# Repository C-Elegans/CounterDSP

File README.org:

* uFluidics Counter Project
This repository is the code for the EE4400 uFluidics Counting Project,
for the dsPIC33fj128gp802. To build, make sure MPLAB X and XC16 are
installed, then run 'make'.

** Circuit
   - Chip: dsPIC33fj128gp802 - dip variant
   - ADC connection
     - Pin AN9, package pin 28
   - SPI:
     - SCK: RP12, pin 23
     - MOSI: RP11, pin 22
     - MISO: RP13, pin 24
     - SS_N: RP14, pin 25
   - Passives:
     - 100nF caps: pin 28, pin 20, pin 13
     - 10uF cap: pin 20
       - *This component is REQUIRED to program the chip*
     - 1k pullup on MCLR_N (pin 1)
   - Supply Voltage
     - 3.25V

** Specifications
   - Analog input signal 200mv pk, unknown waveform
   - Amplified to some level 700mv pk?
   - Sampled at 10kHz
   - Cells counted somehow

# ** DONE List [100%]
#    CLOSED: [2018-03-24 Sat 14:36]
#    - [X] Test the features of the chip [100%]
#      - [X] ADC
#      - [X] UART
#      - [X] SPI
#      - [X] DMA [2/2]
#        - [X] UART
#        - [X] ADC
#      - [X] 80MHz Clock
#      - [X] 10kHz timer
#    - [X] Create A mini oscilloscope
#    - [X] Collect simulated waveform
#      - Waveforms are in data/
#    - [X] Analyze simulated data in matlab, determine best counting method
#      - [X] FFT amplitude
#      - [X] Correlation + threshold
#        - [X] Correlation
#        - [X] Create better correlation waveform. Currently just a sine wave, but
# 	     needs to approximate the triangle-y shape of the actual signal
#        - [X] Proper threshold amount
#    - [X] Program above solution on dsp
#      - Collect 256 samples from ADC
#      - Append them to previous 256 samples
#      - Convert samples to complex, pad with 0s to go to 1024 samples
#      - Run FFT
#      - multiply with FFT of the target waveform (stored in program memory)
#      - run IFFT
#      - Threshold + count
     
** Version 0.2 TODO [16%]
   - [ ] Comment code
   - [X] Clean up code
   - [ ] Add display [0%]
     - [ ] Choose display
     - [ ] Find/Write library
     - [ ] Write display routine
   - [ ] Increase number of channels
     - Goal of 3
   - [ ] Reduce memory usage per channel [0%]
     - [ ] Eliminate ping pong buffer
     - [ ] Copy unused data to X memory
     - [ ] Reduce sample storage [0/3]
       - [ ] Do unbatched correlation + threshold
       - [ ] Reduce size of buffers
       - [ ] Reduce sample rate
   - [ ] Design PCB

** Collected data
#+attr_html: :width 500px
[[./data/data2.png]]

A large nail dropped through a straw, sampled at 5kHz
#+attr_html: :width 500px
[[./data/data4.png]]

A small piece of nail dropped through a straw, 5kHz

* Characterization
** With Two cubic magnets
   - 58mV output from coil
   - 30 turns around straw
   - Straw
     - 5.3mm diameter
     - 
   - ??T field strength
     - Can calculate
     - Measure with hall effect sensor

* Amplifier
** Specifications
   - needs gain of 400mV/600nV=660,000
   - Uses AD8428 as low noise input amplifier (g=2000)
   - Uses ADa4528 as final amplifier
     - Feedback resistors set for g=330, Rf=33k, Rg=100\Omega
   - +- 5V power supply
     - May need to do some scaling with a third amp to feed to DSP
** Simulation
   - Outputs 300mV pk/pk for 300nVpk/pk input
   - 1/f Noise at 50mV
#+attr_html: :width 500px
[[./photos/schematic.png]]
#+attr_html: :width 500px
[[./photos/amp1.png]]

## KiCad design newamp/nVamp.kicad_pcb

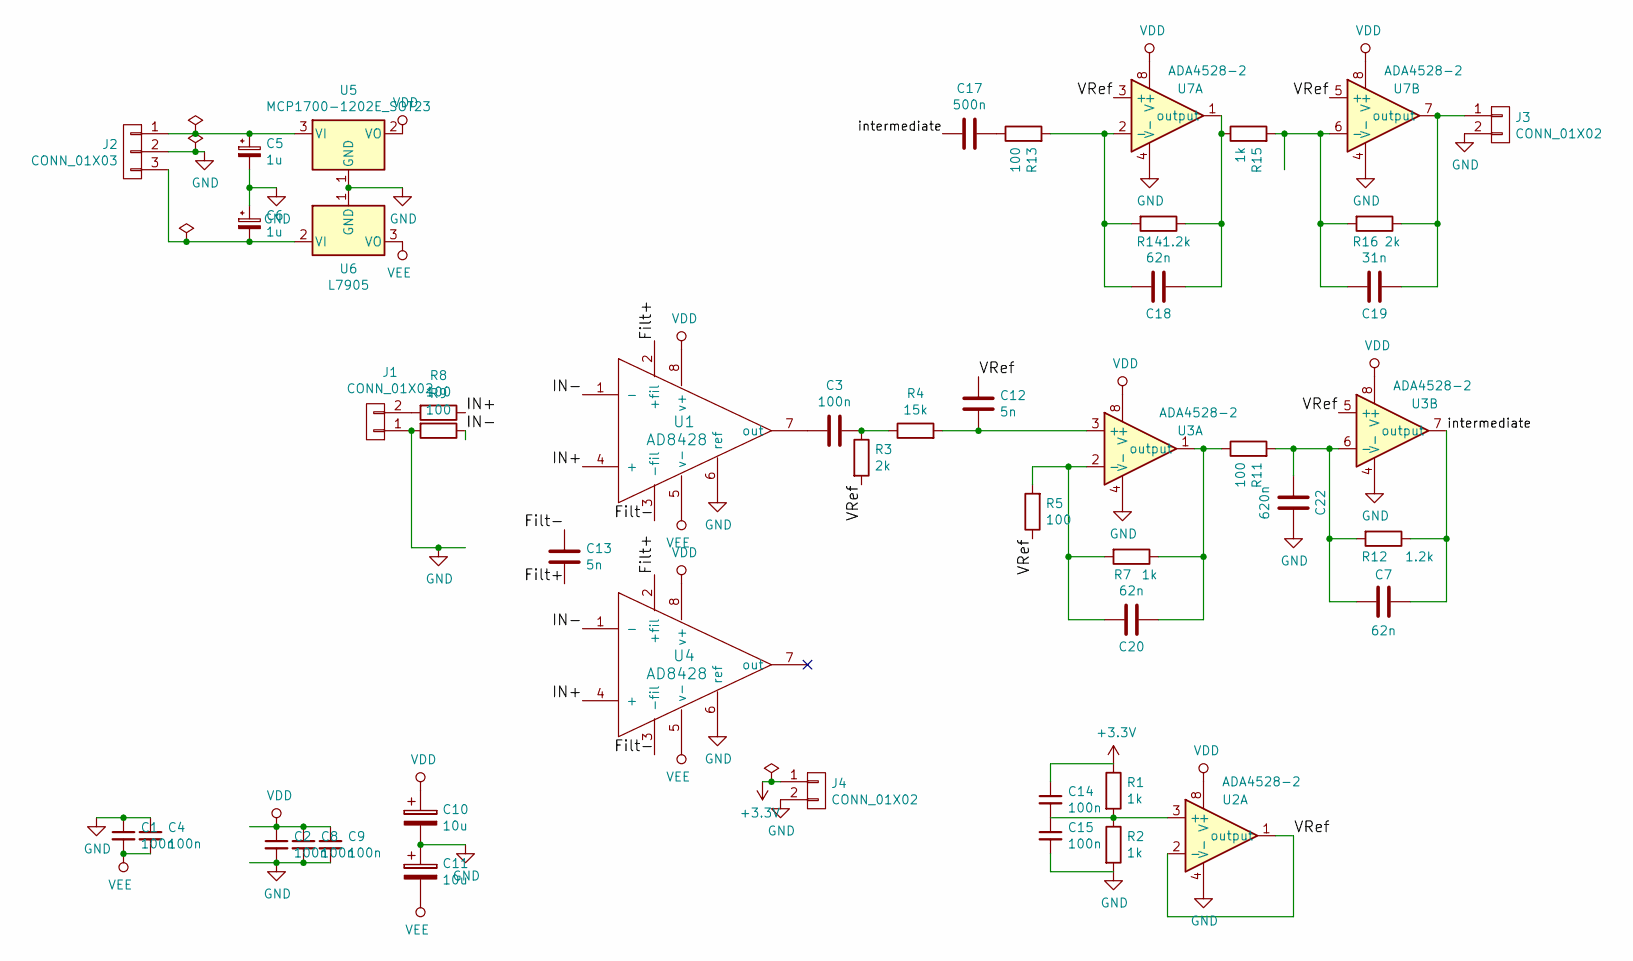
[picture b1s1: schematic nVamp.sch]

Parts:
C1, C2, C3, C4, C8, C9, C14, C15: 100n; C_0603_HandSoldering
C5, C6: 1u; CP_Radial_D5.0mm_P2.50mm
C7, C18, C20: 62n; C_0603_HandSoldering
C10, C11: 10u; CP_Radial_D5.0mm_P2.50mm
C12, C13: 5n; C_0603_HandSoldering
C17: 500n; C_0603_HandSoldering
C19: 31n; C_0603_HandSoldering
C22: 620n; C_0603_HandSoldering
J1, J3, J4: CONN_01X02; Pin_Header_Straight_1x02_Pitch2.54mm
J2: CONN_01X03; Pin_Header_Straight_1x03_Pitch2.54mm
R1, R2, R7, R15: 1k; R_0603_HandSoldering
R3, R16: 2k; R_0603_HandSoldering
R4: 15k; R_0603_HandSoldering
R5, R8, R9, R11, R13: 100; R_0603_HandSoldering
R12, R14: 1.2k; R_0603_HandSoldering
U1, U4: AD8428; SOIC-8_3.9x4.9mm_Pitch1.27mm
U2, U3, U7: ADA4528-2; MSOP-8_3x3mm_Pitch0.65mm
U5: MCP1700-1202E_SOT23; SOT-23
U6: L7905; SOT-89-3

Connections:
+3V3: C14.1, J4.1, R1.1
/Filt+: C13.2, U1.2 (+fil), U4.2 (+fil)
/Filt-: C13.1, U1.3 (-fil), U4.3 (-fil)
/IN+: R8.1, U1.4 (+), U4.4 (+)
/IN-: R9.1, U1.1 (-), U4.1 (-)
/VRef: C12.1, R3.2, R5.1, U2.1 (output), U2.2 (-), U3.5 (+), U7.3 (+), U7.5 (+)
/intermediate: C7.1, C17.2, R12.1, U3.7 (output)
GND: C1.1, C2.2, C4.1, C5.2, C6.1, C8.2, C9.2, C10.2, C11.1, C15.2, C22.1, J1.1, J2.2, J3.2, J4.2, R2.2, R9.2, U1.6 (ref), U2.4 (V-), U3.4 (V-), U4.6 (ref), U5.1 (GND), U6.1 (GND), U7.4 (V-)
unnamed: C3.1, R3.1, R4.1
unnamed: C3.2, U1.7 (out)
unnamed: C5.1, J2.1, U5.3 (VI)
unnamed: C6.2, J2.3, U6.2 (VI)
unnamed: C12.2, R4.2, U3.3 (+)
unnamed: C14.2, C15.1, R1.2, R2.1, U2.3 (+)
unnamed: C17.1, R13.1
unnamed: C18.1, R14.1, R15.1, U7.1 (output)
unnamed: C18.2, R13.2, R14.2, U7.2 (-)
unnamed: C19.1, J3.1, R16.1, U7.7 (output)
unnamed: C19.2, R15.2, R16.2, U7.6 (-)
unnamed: C20.1, R7.1, R11.1, U3.1 (output)
unnamed: C20.2, R5.2, R7.2, U3.2 (-)
unnamed: C7.2, C22.2, R11.2, R12.2, U3.6 (-)
unnamed: J1.2, R8.2
VDD: C2.1, C8.1, C9.1, C10.1, U1.8 (v+), U2.8 (V+), U3.8 (V+), U4.8 (v+), U5.2 (VO), U7.8 (V+)
VEE: C1.2, C4.2, C11.2, U1.5 (v-), U4.5 (v-), U6.3 (VO)

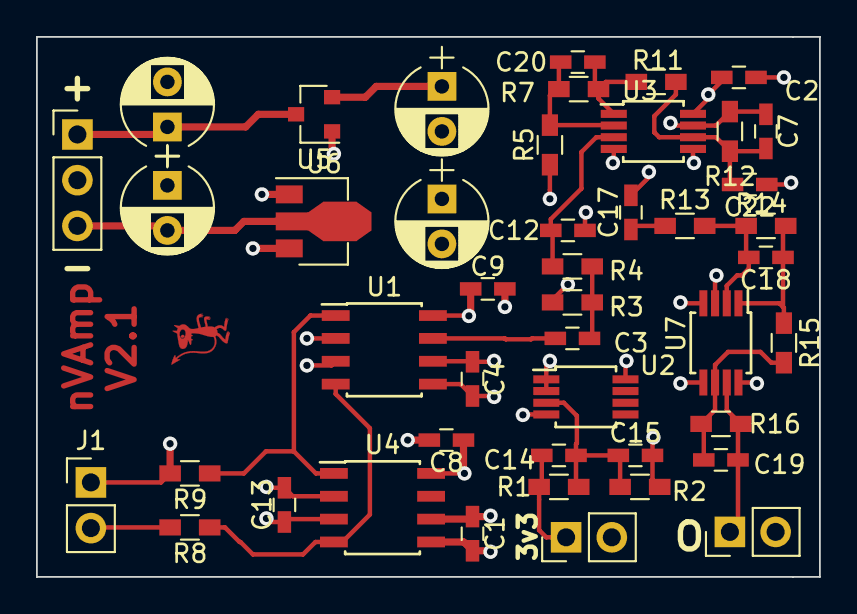
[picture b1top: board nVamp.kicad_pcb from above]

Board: 4 copper layers, 43.5 x 30.0 mm, 45 parts (0 on the bottom side), 25 nets.

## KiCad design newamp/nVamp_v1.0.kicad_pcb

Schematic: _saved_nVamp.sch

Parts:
C1, C2, C4, C5, C6, C7, C8, C9: 100n; C_0603_HandSoldering
C3: 100u; C_1210_HandSoldering
C10, C11: CP; CP_Radial_D8.0mm_P3.50mm
J1, J3, J4: CONN_01X02; Pin_Header_Straight_1x02_Pitch2.54mm
J2: CONN_01X03; Pin_Header_Straight_1x03_Pitch2.54mm
R1, R2: 1k; R_0603_HandSoldering
R3: 15k; R_0603_HandSoldering
R4, R5: 100; R_0603_HandSoldering
R6, R7: 33k; R_0603_HandSoldering
U1, U4: AD8428; SOIC-8_3.9x4.9mm_Pitch1.27mm
U2, U3: ADA4528; TSSOP-8_3x3mm_Pitch0.65mm

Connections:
+3V3: J4.1, R1.1
/Filt+: U1.2 (+fil), U4.2 (+fil)
/Filt-: U1.3 (-fil), U4.3 (-fil)
/IN+: J1.2, U1.4 (+), U4.4 (+)
/VRef: R6.2, U2.2 (-), U2.6
GND: C1.1, C2.2, C4.1, C5.1, C6.1, C7.2, C8.2, C9.2, C10.2, C11.1, J1.1, J2.2, J3.2, J4.2, R2.2, R3.2, R5.1, U1.1 (-), U1.6 (ref), U4.1 (-), U4.6 (ref)
unnamed: C3.1, R3.1, R4.1
unnamed: C3.2, U1.7 (out)
unnamed: J3.1, R7.1, U3.6
unnamed: R1.2, R2.1, U2.3 (+)
unnamed: R4.2, R6.1, U3.3 (+)
unnamed: R5.2, R7.2, U3.2 (-)
VDD: C2.1, C7.1, C8.1, C9.1, C10.1, J2.1, U1.8 (v+), U2.7 (V+), U3.7 (V+), U4.8 (v+)
VEE: C1.2, C4.2, C5.2, C6.2, C11.2, J2.3, U1.5 (v-), U2.4 (V-), U3.4 (V-), U4.5 (v-)

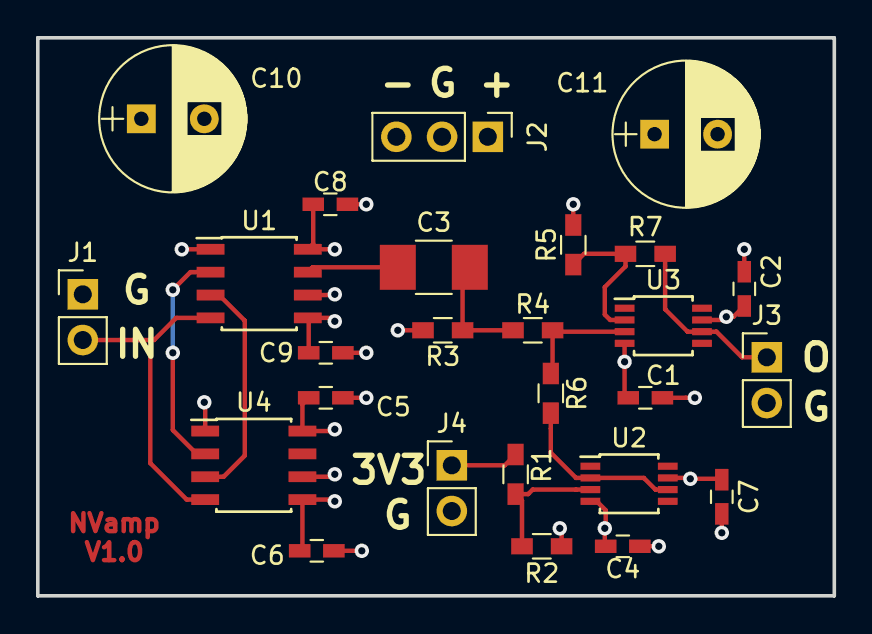
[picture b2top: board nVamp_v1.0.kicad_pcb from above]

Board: 4 copper layers, 44.2 x 31.0 mm, 26 parts (0 on the bottom side), 14 nets.

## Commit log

2017-12-28 Use the MPLib UART functions for printing
2018-01-11 setup ADC to work with DMA
2018-01-11 Move configuration to config.h
2018-01-11 Set DMA to ping pong mode, fix indentation for emacs
2018-01-11 Add some documentation
2018-01-11 Add license and readme
2018-01-12 Get Chip working + UART
2018-01-12 Test adc
2018-01-12 Add TODO list to readme
2018-01-13 Add project configuration to the repo (oops)
2018-01-13 Move peripheral configuration to separate file
2018-01-13 Get SPI working (though very simply)
2018-01-13 Create PLL parameter calculator
2018-01-13 80MHz clock working
    Had some difficulties with programming, turns out a 10uF cap to Vcap
    is required for correct operation.
2018-01-13 Get uart working at 1Mbaud
2018-01-13 ADC DMA transfers working
2018-01-14 Configure ADC to sample off Timer3
    Now ADC samples at 10kHz and the buffer of samples gets sent to the
    host computer over 1Mbaud uart
2018-01-14 Get mini oscilloscope working
2018-01-14 Command line programming script
2018-01-14 Collect some sample waveforms
2018-01-14 Add data from smaller magnets, begin data analysis
2018-01-15 Cleanup scope.py
2018-01-15 Update the matlab analysis script
    Analyzes the input signal and plots an fft of the data as well as
    correlating the data with a single sine wave of a similar frequency to
    the input pulse.
2018-01-15 Move mcu sources to separate folder
2018-01-16 Collect data with two magnets dropped
2018-01-16 Use FFT for convolution instead of plain convolution
2018-01-20 Outline plan for the final program
2018-01-20 Analyze program's behavior with regard to 1/f noise
2018-01-20 Increase the scope baud rate to 500Kbaud
2018-01-22 Add schematic of measurement circuit
2018-01-22 Add argument for creating a new amplifier
2018-01-23 Add opamp selection criteria and candidates
2018-01-23 Begin PCB design
2018-01-23 Add thoughts on connections between amps
2018-01-24 Begin working on amp simulation
2018-01-24 Add scope trigger argument to command line
2018-01-24 Add simulation of AD8248
2018-01-24 Test DC blocking high pass filter
2018-01-24 Simulate full amplifier
    100nV 10Hz signal ->
    AD8428 instrumentation amplifier ->
    RC high pass filter with fc=0.1Hz ->
    AD4528 op amp with gain 1000 ->
    200mV 10Hz signal
2018-01-24 Update PCB to use AD8428 and AD4528 amps
2018-01-24 Add transient noise source
    Approximate the noise from the first amplifier stage
2018-01-24 Add amp info to README
2018-01-24 Add schematic image to README
2018-01-30 Pretty up schematics
2018-01-30 Generate emacs ctags when building a project
2018-01-30 Add some routines for signal processing
    scalepadbuffer - Scales input signal to -0.5-0.5, centers it around 0,
    and copies it to the destination buffer with 0 padding
    vmul - multiplies a transformed signal by another
2018-01-30 Add twiddle factors and FFT call to project
2018-01-30 Add script to calculate FFT twiddle factors
2018-01-30 Use FFT+IFFT for scope data
2018-01-30 Do not scale fft output for uart
2018-01-30 Begin migrating to discrete convolution implementation
2018-01-30 Fix errors in last commit
2018-01-30 Add project configuration
2018-01-30 Move twiddle generator to python for easier use
    Also generate conjugate twiddle factors
2018-01-30 Window the FFT
    FFT overlaps previous buffer by 256
2018-01-30 Square the signal and use convolution in analysis.m
2018-01-30 Create convolution signal generator
    Actually approximate a triangle wave in analyisis.m
2018-01-30 Add count_spikes which counts the spikes in the convolved signal
2018-01-30 Remove twid.c (no fft so no need for twiddle factors)
2018-01-30 Move some functions to periph.c
2018-01-30 (Hopefully) convolve 'sig' with the input buffer
2018-01-31 Try to view waveform with overlapped samples
2018-01-31 Scale convolution kernel so that the output does not overflow
2018-01-31 Convolve and square the input signal
    Write a separate vector square function because vmul needs one input
    to be in x space and one input to be in y space
2018-01-31 Update makefile configuration
2018-01-31 Change the targets of DO loops to use local labels
2018-02-01 Some minor asm optimizations
2018-02-05 Modify schematic so it looks nicer
2018-02-05 Capture some data from convolved+squared signal
2018-02-05 Count pulses
2018-02-12 Update PCB to use two AD8428s for lower noise
2018-02-14 Make a better, 4 layer design for nVamp
2018-02-14 Modify matlab script to generate nice(r) figures
2018-02-14 Add Doc on DSP process
2018-02-14 Add section describing the code on the DSP
2018-03-07 Add more documentation
2018-03-24 Update amplifier
2018-03-24 Add picture of amplifier
2018-03-24 Some makefile changes
2018-03-24 Add todo list for version 0.2
2018-03-24 Comment main.c and convolve.s
2018-03-29 Update spice schematic
2018-04-11 Add noise analysis & data
2018-04-23 Update schematics to add filters and AD4528 single supply
2018-05-03 Add differential input to simulation
2018-05-04 Redo amplifier schematic in ltspice Add some pictures of the output New amplifier has a lot more filtering, as well as a differential input
2018-05-04 Add section on amplifier revision to dsp.pdf
2018-05-04 Begin working on v2 pcb
2018-09-18 Finished version 2.0 of the amplifier PCB
    Add better filtering from Ben,
    Add differential input
2018-12-07 Lots of changes
2021-03-23 Add sources in src/ folder
